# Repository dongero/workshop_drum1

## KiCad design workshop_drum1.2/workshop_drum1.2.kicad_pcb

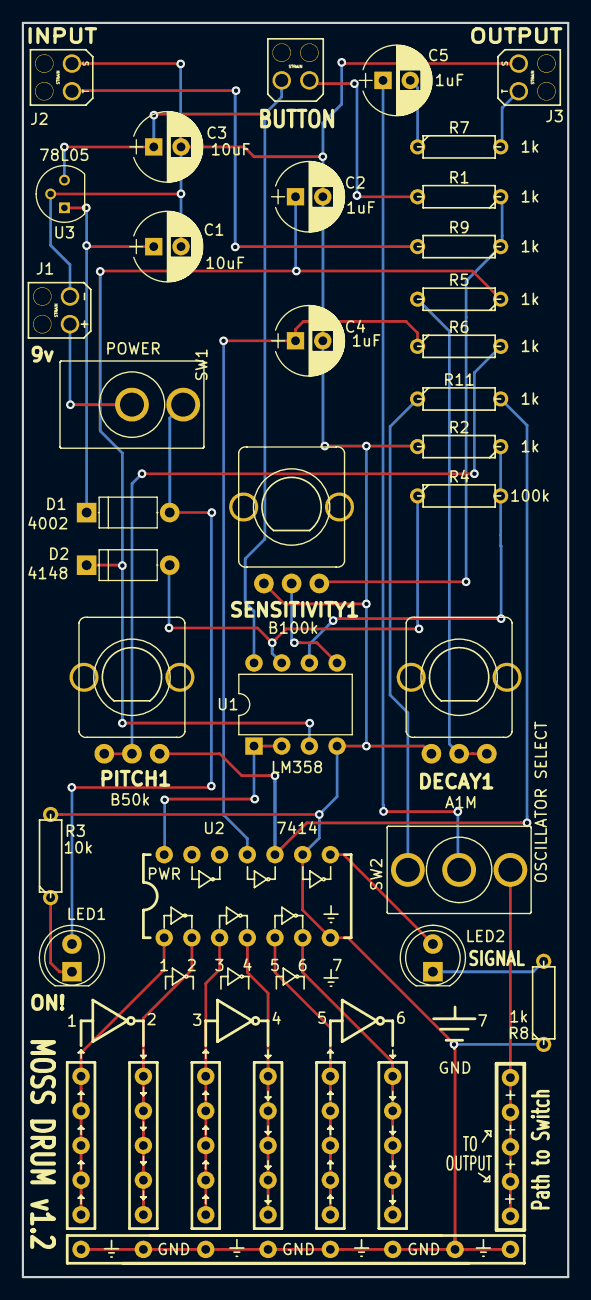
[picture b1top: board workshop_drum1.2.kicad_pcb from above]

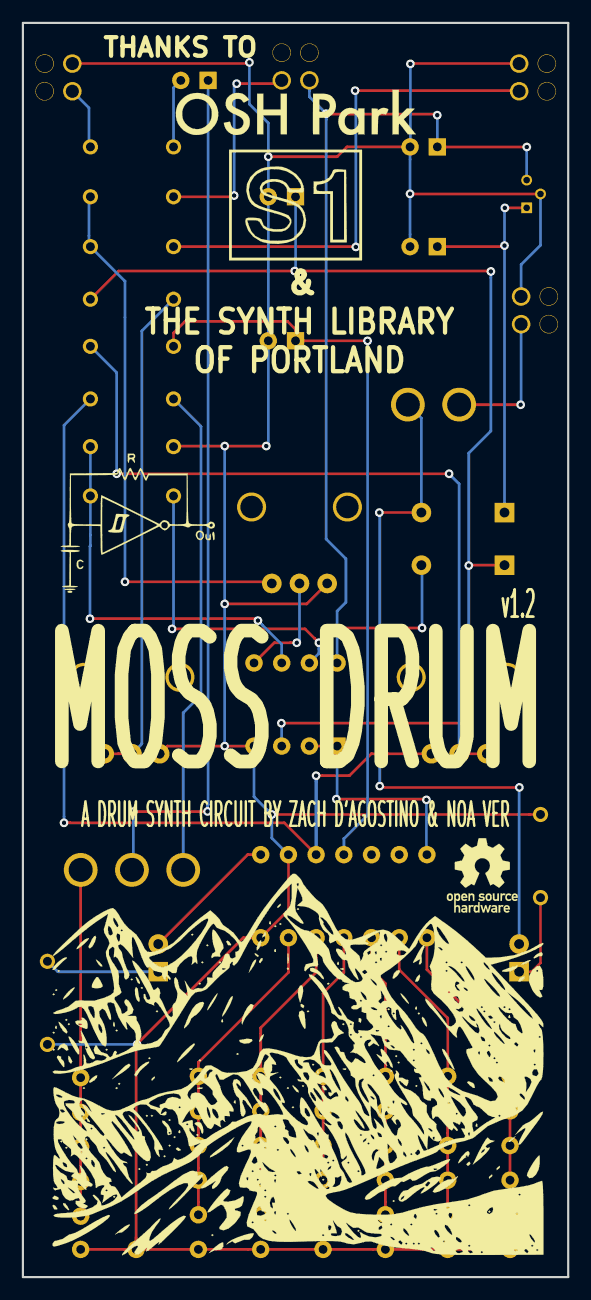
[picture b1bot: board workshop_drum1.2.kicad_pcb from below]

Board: 2 copper layers, 50.0 x 115.0 mm, 37 parts (5 on the bottom side), 25 nets.

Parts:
BreadBoardStrip1: Path to Switch; BREAKOUTswitch
C1, C3: 10uF; Cap_Electrolytic_TH
C2, C4, C5: 1uF; Cap_Electrolytic_TH
D1: 4002; Diode_BAT-85S_TH
D2: 4148; Diode_BAT-85S_TH
DECAY1: A1M; POT-9MM-ALPHA
J1: 9v; 9v_Bigger
J2: INPUT; Jack_Instrument_Bigger
J3: OUTPUT; Jack_Instrument_Bigger
LED1: ON!; LED_D5.0mm
LED2: SIGNAL; LED_D5.0mm
LOGO1: Open; Logo_Open-3
LOGO2: S1; S1SMalllllllaf
LOGO3: OSH; Logo_OSH-4
LOGO4: OSC; Logo_OSC-1
LOGO5: MNT; Logo_MNT-2
PITCH1: B50k; POT-9MM-ALPHA
R1, R2, R5, R6, R7, R8, R9, R11: 1k; Resistor_TH_300
R3: 10k; Resistor_TH_300
R4: 100k; Resistor_TH_300
SENSITIVITY1: B100k; POT-9MM-ALPHA
SW1: POWER; Switch_Toggle_SPST_Mini_SolderLug_2legs_Circle
SW2: OSCILLATOR SELECT; Switch_Toggle_SPDT_Mini_SolderLug_Circle
SW3: BUTTON; Button_Bigger
U1: LM358; DIP_8pin_TL082_TH_CenteredNotOnPin1
U2: 7414; BREAKOUT
U3: 78L05; TO-92_Molded_Narrow

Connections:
+5V: C3.1, SW3.2, U1.8, U3.3
GND: C1.2, C2.2, C3.2, C4.2, DECAY1.1, J1.2, J2.2, J3.2, R2.2, R3.2, R8.1, SENSITIVITY1.1, U1.4, U2.7, U2.9, U3.2
unnamed: BreadBoardStrip1.1, SW2.3
unnamed: C1.1, D1.1, U3.1
unnamed: C2.1, D2.1, R5.1, U1.3
unnamed: C4.1, R6.1, U2.11
unnamed: C5.1, SW2.2
unnamed: C5.2, R7.1
unnamed: D1.2, LED1.2, SW1.1
unnamed: D2.2, R4.1, U1.7
unnamed: DECAY1.2, DECAY1.3, R5.2
unnamed: J1.1, SW1.2
unnamed: J2.1, R9.2
unnamed: J3.1, R7.2
unnamed: LED1.1, R3.1
unnamed: LED2.1, R8.2
unnamed: LED2.2, U2.8
unnamed: PITCH1.1, PITCH1.2, R6.2
unnamed: PITCH1.3, R11.2, U2.10
unnamed: R1.1, R9.1, SENSITIVITY1.3
unnamed: R1.2, SW3.1
unnamed: R2.1, R4.2, U1.6
unnamed: R11.1, SW2.1
unnamed: SENSITIVITY1.2, U1.5
unnamed: U1.1, U1.2, U2.14

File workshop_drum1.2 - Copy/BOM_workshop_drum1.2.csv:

"Id";"Designator";"Package";"Quantity";"Designation";"Supplier and ref";
1;"SW2";"Switch_Toggle_SPDT_Mini_SolderLug_Circle";1;"OSCILLATOR SELECT";;;
2;"SW1";"Switch_Toggle_SPST_Mini_SolderLug_2legs_Circle";1;"POWER";;;
3;"LOGO1";"Logo_Open-3";1;"Open";;;
4;"LOGO3";"Logo_OSH-3";1;"OSH";;;
5;"LOGO2";"Logo_S1-2";1;"S1";;;
6;"SW3";"Button_Bigger";1;"BUTTON";;;
7;"J1";"9v_Bigger";1;"9v";;;
8;"U2";"BREAKOUT";1;"7414";;;
9;"J2";"Jack_Instrument_Bigger";1;"INPUT";;;
10;"J3";"Jack_Instrument_Bigger";1;"OUTPUT";;;
11;"R11,R8,R7,R6,R5,R2,R1,R9";"Resistor_TH_300";8;"1k";;;
12;"U1";"DIP_8pin_TL082_TH_CenteredNotOnPin1";1;"LM358";;;
13;"BreadBoardStrip1";"BREAKOUTswitch";1;"Path to Switch";;;
14;"LED1";"LED_D5.0mm";1;"ON!";;;
15;"LED2";"LED_D5.0mm";1;"SIGNAL";;;
16;"C5";"Cap_Ceramic_TH";1;"100nf";;;
17;"C1,C3";"Cap_Electrolytic_TH";2;"10uF";;;
18;"C2,C4";"Cap_Electrolytic_TH";2;"1uF";;;
19;"D2";"Diode_BAT-85S_TH";1;"4148";;;
20;"D1";"Diode_BAT-85S_TH";1;"4002";;;
21;"R4";"Resistor_TH_300";1;"100k";;;
22;"R3";"Resistor_TH_300";1;"10k";;;
23;"U3";"TO-92_Molded_Narrow";1;"78L05";;;
24;"DECAY1";"POT-9MM-ALPHA";1;"A1M";;;
25;"PITCH1";"POT-9MM-ALPHA";1;"B50k";;;
26;"SENSITIVITY1";"POT-9MM-ALPHA";1;"B100k";;;
27;"LOGO5";"Logo_MNT-2";1;"MNT";;;
28;"LOGO4";"Logo_OSC-1";1;"OSC";;;

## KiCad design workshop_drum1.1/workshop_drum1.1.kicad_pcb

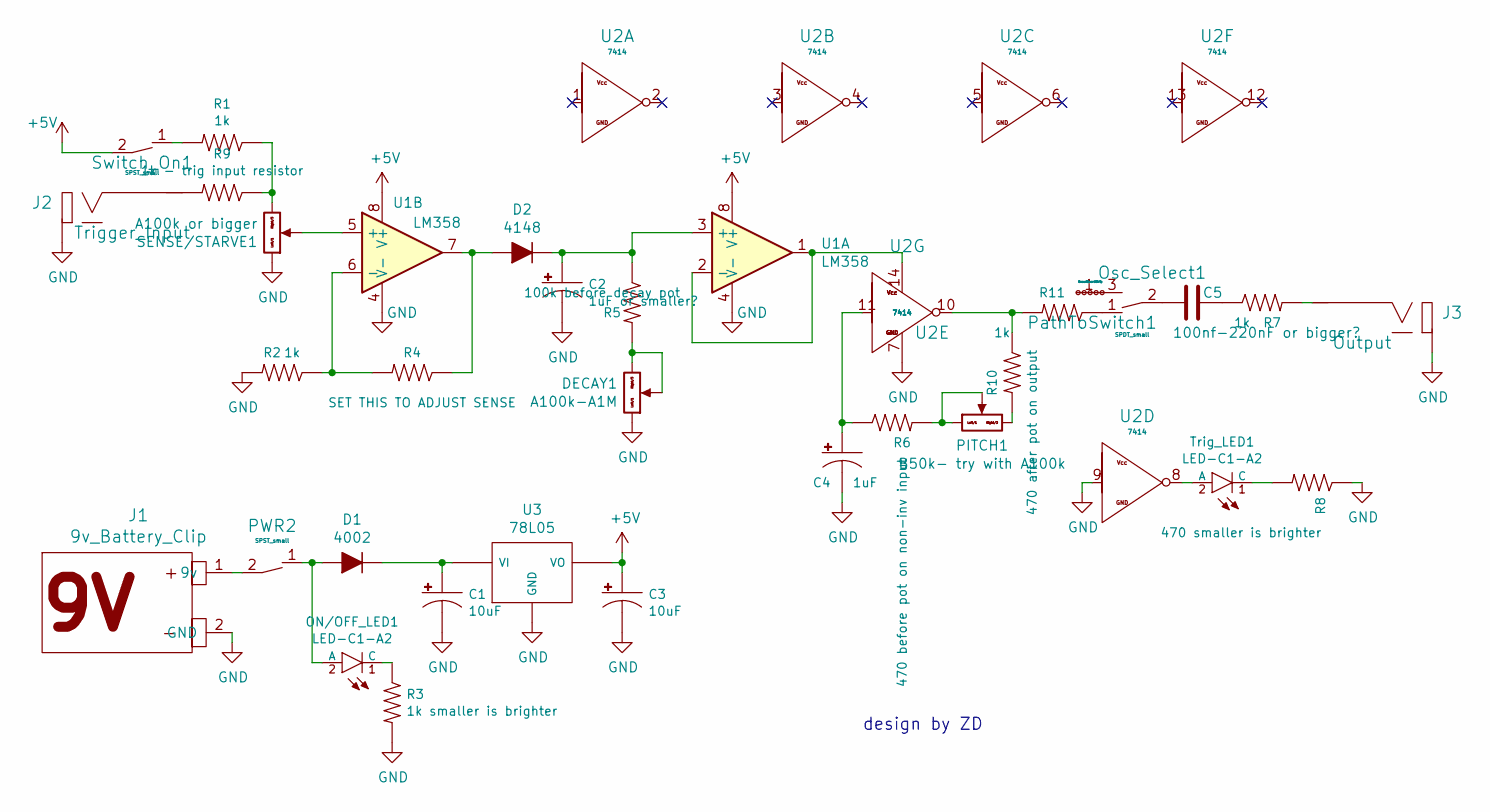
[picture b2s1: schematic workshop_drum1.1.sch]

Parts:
C1, C3: 10uF; Cap_Electrolytic_TH
C2: 1uF or smaller?; Cap_Electrolytic_TH
C4: 1uF; Cap_Electrolytic_TH
C5: 100nf-220nF or bigger?; Cap_Ceramic_TH
D1: 4002; Diode_BAT-85S_TH
D2: 4148; Diode_BAT-85S_TH
DECAY1: A100k-A1M; POT-9MM-ALPHA
J1: 9v_Battery_Clip; Jack_Instrument_Bigger
J2: Trigger_Input; Jack_Instrument_Bigger
J3: Output; Jack_Instrument_Bigger
ON/OFF_LED1: LED-C1-A2; LED_D5.0mm
Osc_Select1: SPDT_small; Switch_Toggle_SPDT_Mini_SolderLug
PITCH1: B50k- try with A100k; POT-9MM-ALPHA
PWR2: SPST_small; Switch_Toggle_SPST_Mini_SolderLug_2legs
PathToSwitch1: BreadBoardStrip; BREAKOUTswitch
R1, R2, R7, R11: 1k; Resistor_TH_300
R3: 1k smaller is brighter; Resistor_TH_300
R4: SET THIS TO ADJUST SENSE; Resistor_TH_300
R5: 100k before decay pot; Resistor_TH_300
R6: 470 before pot on non-inv input; Resistor_TH_300
R8: 470 smaller is brighter; Resistor_TH_300
R9: 1k - trig input resistor; Resistor_TH_300
R10: 470 after pot on output; Resistor_TH_300
SENSE/STARVE1: A100k or bigger; POT-9MM-ALPHA
Switch_On1: SPST_small; Jack_Instrument_Bigger
Trig_LED1: LED-C1-A2; LED_D5.0mm
U1: LM358; DIP_8pin_TL082_TH_CenteredNotOnPin1
U2: 7414; BREAKOUT
U3: 78L05; TO-92_Molded_Narrow

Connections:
+5V: C3.1 (+), Switch_On1.2, U1.8 (V+), U3.3 (VO); also elsewhere on the board
GND: C1.2 (-), C2.2 (-), C3.2 (-), C4.2 (-), DECAY1.1 (Left), J1.2 (GND), J2.2 (GND), J3.2 (GND), R2.2, R3.2, R8.1, SENSE/STARVE1.1 (Left), U1.4 (V-), U2.7, U2.9, U3.2 (GND)
unnamed 2: R1.2, Switch_On1.1; also elsewhere on the board
unnamed: C1.1 (+), D1.1 (K), U3.1 (VI)
unnamed: C2.1 (+), D2.1 (K), R5.1, U1.3 (+)
unnamed: C4.1 (+), R6.1, U2.11
unnamed: C5.1, R7.1
unnamed: C5.2, Osc_Select1.2
unnamed: D1.2 (A), ON/OFF_LED1.2 (A), PWR2.1
unnamed: D2.2 (A), R4.1, U1.7
unnamed: DECAY1.2 (Center), DECAY1.3 (Right), R5.2
unnamed: J1.1 (9v), PWR2.2
unnamed: J2.1 (V), R9.2
unnamed: J3.1 (V), R7.2
unnamed: ON/OFF_LED1.1 (C), R3.1
unnamed: Osc_Select1.1, R11.1
unnamed: Osc_Select1.3, PathToSwitch1.1
unnamed: PITCH1.1 (Left), PITCH1.2 (Center), R6.2
unnamed: PITCH1.3 (Right), R10.2
unnamed: R1.1, R9.1, SENSE/STARVE1.3 (Right)
unnamed: R2.1, R4.2, U1.6 (-)
unnamed: R8.2, Trig_LED1.1 (C)
unnamed: R10.1, R11.2, U2.10
unnamed: SENSE/STARVE1.2 (Center), U1.5 (+)
unnamed: Trig_LED1.2 (A), U2.8
unnamed: U1.1, U1.2 (-), U2.14

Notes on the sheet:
design by ZD

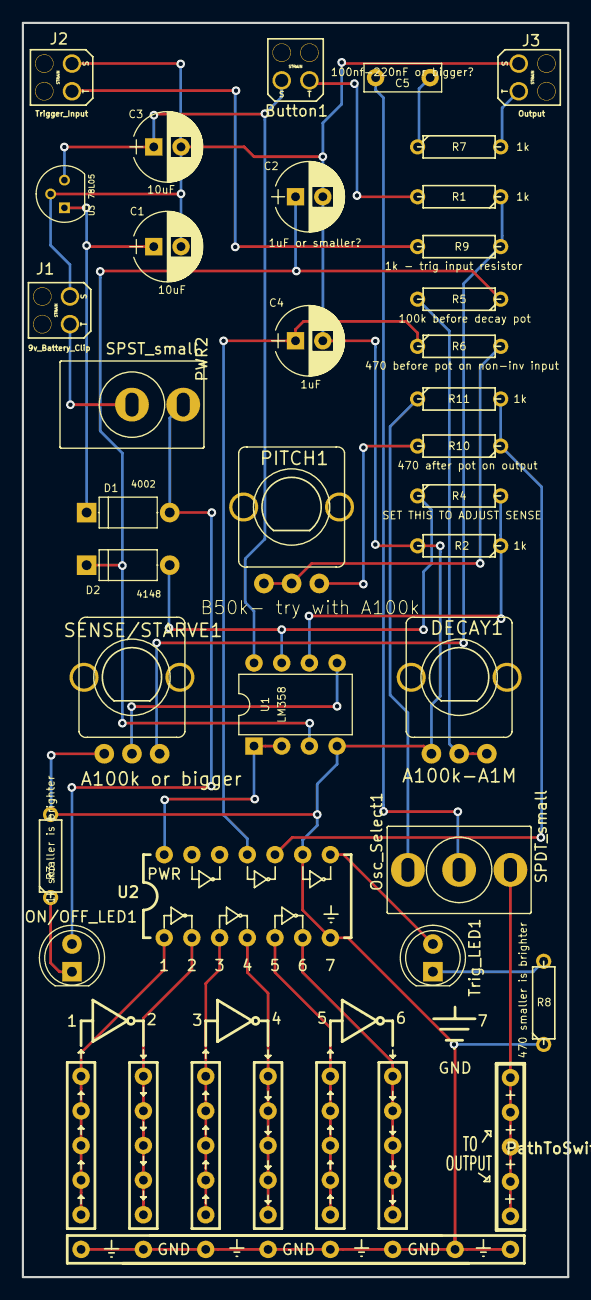
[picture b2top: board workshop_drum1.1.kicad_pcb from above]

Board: 2 copper layers, 50.0 x 115.0 mm, 33 parts (0 on the bottom side), 26 nets.

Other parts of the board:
Button1: SPST_small; Jack_Instrument_Bigger

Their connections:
+5V: Button1.2; also elsewhere on the board
unnamed 2: Button1.1; also elsewhere on the board

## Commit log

2017-12-14 first commit - hope it works ok
2017-12-14 testing
2017-12-14 test#2
2017-12-14 started project
2017-12-14 setup sch files and libraries on work comp
2017-12-14 nicknamed 4ms lib to Z4ms for single project, rather than all projects
2017-12-14 ready to build schematic
2017-12-14 schematic laid out - started PCB
2017-12-14 finished first look of schematic
2017-12-14 CRUISIN'
2017-12-14 places breadboard section in better spot
2017-12-15 connected traces
2017-12-15 ready to send in
2017-12-15 made gerbers - looked at gerbv
2017-12-28 got rid of square pins - printed gerbers - changed names- relayed traces
2018-03-27 Started DRUM2 folder - changed pots, switches and took out a few parts
2018-03-28 P1.1 - Updated footprints prior to deleting PCB
2018-03-28 P1.1 started working on breadboard strip
2018-03-29 re organizing boards with breakout footprints
2018-03-29 starting to lay traces
2018-03-29 Continued work on the pcb layout
2018-03-30 Ready for review
2018-03-30 made gerbers - relocated pcb
2018-04-16 Started workshop_drum1.2
2018-04-16 -WIP-
2018-04-21 About to update from SCHEM after doing logos
2018-04-22 Made PCB look cool - but havent updated from sch yet
2018-04-23 Ordered v1.2 - generated gerbers and arranged artwork
2018-05-05 redid silk - this is the one sent to OSH 5/4/18
2018-05-06 changed C5 from 100nf to 1uF - ceramic to elect cap - generated grbs
2018-05-06 forgot to save
2018-09-09 most updated folder
